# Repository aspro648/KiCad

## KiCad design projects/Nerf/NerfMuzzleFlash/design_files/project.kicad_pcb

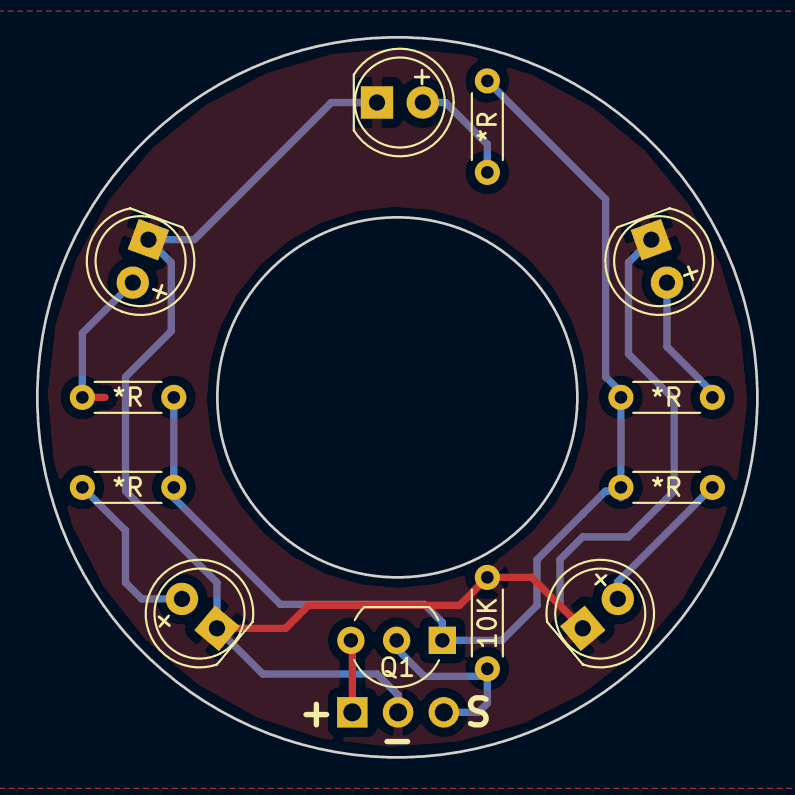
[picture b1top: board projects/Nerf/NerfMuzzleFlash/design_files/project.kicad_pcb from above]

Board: 2 copper layers, 40.0 x 40.0 mm, 13 parts (0 on the bottom side), 9 nets.

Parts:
D1, D2, D3, D4, D5: LED; LED_D5.0mm
J1: CONN_01X03; Pin_Header_Straight_1x03_Pitch2.54mm
Q1: TN0702; TO-92_Inline_Wide
R1, R2, R3, R4, R5: *R; R_Axial_P5.08mm
R6: 10K; R_Axial_P5.08mm

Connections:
GND: D1.1, D2.1, D3.1, D4.1, D5.1, J1.2, R6.1
unnamed: D1.2, R1.1
unnamed: D2.2, R2.1
unnamed: D3.2, R3.1
unnamed: D4.2, R4.1
unnamed: D5.2, R5.1
unnamed: J1.1, Q1.3
unnamed: J1.3, Q1.2, R6.2
unnamed: Q1.1, R1.2, R2.2, R3.2, R4.2, R5.2

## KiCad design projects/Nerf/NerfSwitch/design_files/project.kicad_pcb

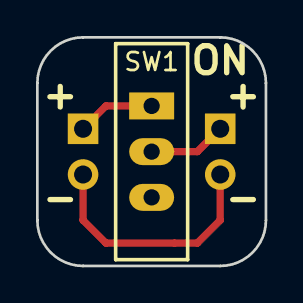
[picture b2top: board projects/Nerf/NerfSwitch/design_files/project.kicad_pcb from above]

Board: 2 copper layers, 12.7 x 12.7 mm, 3 parts (0 on the bottom side), 3 nets.

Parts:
J1, J2: CONN_01X02; Pin_Header_Straight_1x02_Pitch2.54mm
SW1: SW_SPST; SW_CuK_OS102011MA1QN1_SPDT_Angled

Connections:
unnamed: J1.1, SW1.1
unnamed: J1.2, J2.2
unnamed: J2.1, SW1.2

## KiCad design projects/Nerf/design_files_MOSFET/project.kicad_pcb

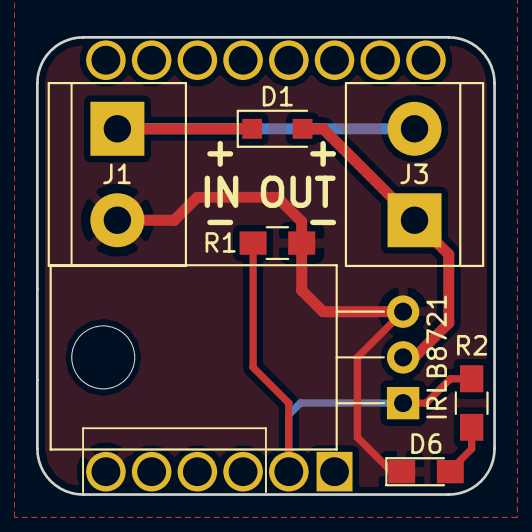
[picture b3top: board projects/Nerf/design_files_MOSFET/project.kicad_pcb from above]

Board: 2 copper layers, 25.4 x 25.4 mm, 10 parts (0 on the bottom side), 5 nets.

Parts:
D1: D; D_SOD-123F
D6: LED; LED_0805_HandSoldering
J1, J3: Conn_01x02; TerminalBlock_bornier-2_P5.08mm
J2: Beetje_Bottom
J4: Beetje_Top
Q1: IRLB8721; TO-220-3_Horizontal
R1: 10K; R_0805_HandSoldering
R2: 1K; R_0805_HandSoldering
VAL: MadeInOregonRev25

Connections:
/D6: J2.2, Q1.1, R1.1, R2.2
GND: D6.1, J1.2, J2.6, Q1.3, R1.2
unnamed: D1.1, J1.1, J3.2
unnamed: D1.2, J3.1, Q1.2
unnamed: D6.2, R2.1

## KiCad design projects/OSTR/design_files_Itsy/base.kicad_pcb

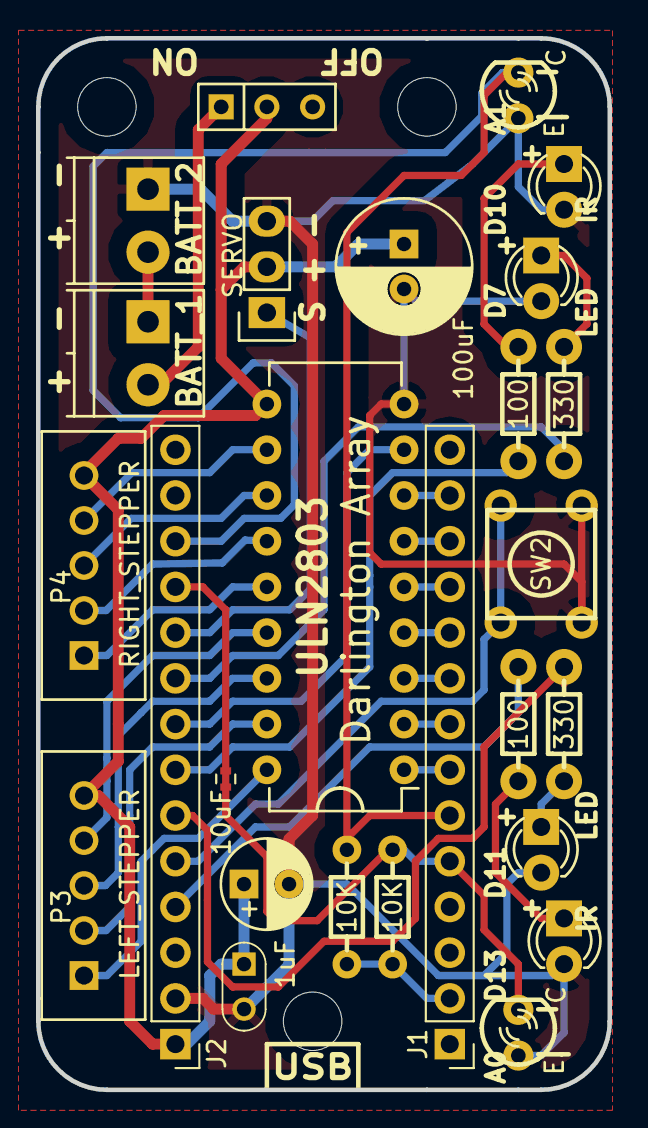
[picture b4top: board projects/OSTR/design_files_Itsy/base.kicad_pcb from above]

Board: 2 copper layers, 31.8 x 58.4 mm, 32 parts (1 on the bottom side), 33 nets.

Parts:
C1: 100uF; C_Radial_D7.5_L11.2_P2.5
C2: 10uF; C_Radial_D5_L11_P2.5
C3: 1uF; C_Disc_D3_P2.5
D2: IR_LED; LED-3MM
D3, D4: LED; LED-3MM
D5: IR LED; LED-3MM
J1: Isty_Left; Pin_Header_Straight_1x14_Pitch2.54mm
J2: Itsy_right; Pin_Header_Straight_1x14_Pitch2.54mm
P3: LEFT_STEPPER; JST_B5B-XH-A
P4: RIGHT_STEPPER; JST_B5B-XH-A
P5: BATT1; TerminalBlock_Pheonix_PT-3.5mm_2pol
P6: BATT2; TerminalBlock_Pheonix_PT-3.5mm_2pol
P7: SERVO; Pin_Header_Straight_1x03
P9, P9#2, P9#3: CONN_01X01; Lego_Pad
Q1, Q2: OPTO_NPN; PHOTOTRANS
R1, R8: 0; R_0402
R2, R5: 100; Resistor_Horz
R3, R4: 330; Resistor_Horz
R6, R7: 10K; Resistor_Horz
SW1: SPST; SW_Micro_SPST
SW2: SW_PUSH; SW_PUSH_SMALL
U1: ULN2803; DIP-18_W7.62mm
VAL: MadeInOregonRev25
VAL#2: MB225rev

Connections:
+3V3: J1.2, R6.1, R7.1
/A0: J1.5, J2.11, Q2.3, R6.2, R8.1, R8.2
/A1: J1.6, J2.12, Q1.3, R1.1, R1.2, R7.2
/A2: J1.7, U1.1
/A3: J1.8, U1.2
/A4: J1.9, U1.3
/A5: J1.10, U1.4
/BAT: C1.1, C2.1, C3.1, J2.1, P3.5, P4.5, P7.2, SW1.2, U1.10
/D5: J2.10, P7.1
/D7: J2.9, R3.1
/D9: J2.8, U1.8
/D10: J2.7, R5.1
/D11: J2.6, R4.1
/D12: J2.5, SW2.1
/D13: J2.4, R2.1
/D14: J1.13, U1.7
/D15: J1.11, U1.5
/D16: J1.12, U1.6
GND: C1.2, C2.2, C3.2, D2.1, D3.1, D4.1, D5.1, J2.2, P5.1, P7.3, Q1.1, Q2.1, SW2.2, U1.9
unnamed: D2.2, R2.2
unnamed: D3.2, R3.2
unnamed: D4.2, R4.2
unnamed: D5.2, R5.2
unnamed: P3.1, U1.18
unnamed: P3.2, U1.17
unnamed: P3.3, U1.16
unnamed: P3.4, U1.15
unnamed: P4.1, U1.14
unnamed: P4.2, U1.13
unnamed: P4.3, U1.12
unnamed: P4.4, U1.11
unnamed: P5.2, P6.1
unnamed: P6.2, SW1.1

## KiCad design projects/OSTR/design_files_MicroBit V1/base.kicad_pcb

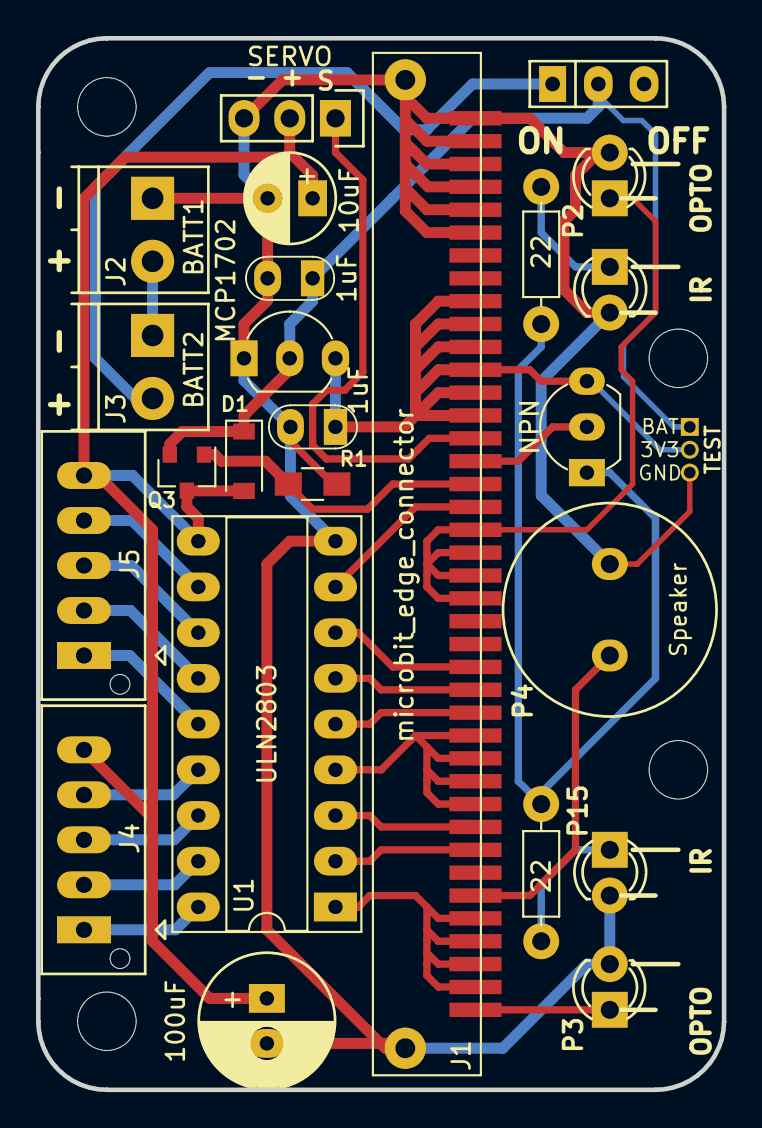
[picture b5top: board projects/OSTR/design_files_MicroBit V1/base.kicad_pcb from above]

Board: 2 copper layers, 38.1 x 58.4 mm, 31 parts (0 on the bottom side), 31 nets.

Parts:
C1: 100uF; C_Radial_D7.5_L11.2_P2.5
C2: 10uF; C_Radial_D5_L11_P2.5
C3, C4: 1uF; C_Disc_D3_P2.5
D1: D; D_SOD-123
D2: IR_LED; LED-3MM
D5: IR LED; LED-3MM
J1: microbit_edge_connector; MicroBit40
J2: BATT1; TerminalBlock_Pheonix_PT-3.5mm_2pol
J3: BATT2; TerminalBlock_Pheonix_PT-3.5mm_2pol
J4: LEFT_STEPPER; JST_B5B-XH-A
J5: RIGHT_STEPPER; JST_B5B-XH-A
J6: SERVO; Pin_Header_Straight_1x03
J7: TEST; Pin_Header_Straight_1x03_Pitch1.27mm
LS1: Speaker; SPEAKER
P9, P9#2, P9#3, P9#4: CONN_01X01; Lego_Pad
Q1, Q2: OPTO; LED-3MM
Q3: MOSFET; SOT-23
Q4: NPN; TO-92_Inline_Wide
R1: 10K; R_0805_HandSoldering
R2, R5: 22; R__7.62mm
SW1: SPST; SW_Micro_SPST
U1: ULN2803; DIP-18_W7.62mm_Socket_LongPads
U2: MCP1702; TO-92_Inline_Wide
VAL: MadeInOregonRev25
VAL#2: MB225rev

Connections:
+3V3: C3.1, J1.17, J1.19, J1.21, J1.23, J1.25, J1.27, J7.2, Q4.3, U2.3
/BAT: C4.1, D1.1, J7.1, Q3.2, SW1.2, U2.2
/P0: J1.71, J1.73, J1.75, J1.77, U1.1
/P1: J1.55, J1.57, J1.59, J1.61, U1.4
/P2: J1.37, J1.39, J1.41, J1.43, Q1.3
/P3: J1.79, Q2.3
/P4: J1.69, LS1.1
/P6: J1.65, U1.2
/P7: J1.63, U1.3
/P8: J1.53, U1.5
/P9: J1.51, U1.6
/P10: J1.49, U1.7
/P13: J1.35, U1.8
/P14: J1.33, Q3.1, R1.1
/P15: J1.31, Q4.2
/P16: J1.29, J6.1
GND: C1.2, C2.2, C3.2, C4.2, D2.1, D5.1, J1.1, J1.3, J1.5, J1.7, J1.9, J1.11, J2.1, J6.3, J7.3, LS1.2, Q1.1, Q2.1, R1.2, U1.9, U2.1
unnamed: C1.1, C2.1, D1.2, J4.5, J5.5, J6.2, Q3.3, U1.10
unnamed: D2.2, R2.2
unnamed: D5.2, R5.2
unnamed: J2.2, J3.1
unnamed: J3.2, SW1.1
unnamed: J4.1, U1.18
unnamed: J4.2, U1.17
unnamed: J4.3, U1.16
unnamed: J4.4, U1.15
unnamed: J5.1, U1.14
unnamed: J5.2, U1.13
unnamed: J5.3, U1.12
unnamed: J5.4, U1.11
unnamed: Q4.1, R2.1, R5.1

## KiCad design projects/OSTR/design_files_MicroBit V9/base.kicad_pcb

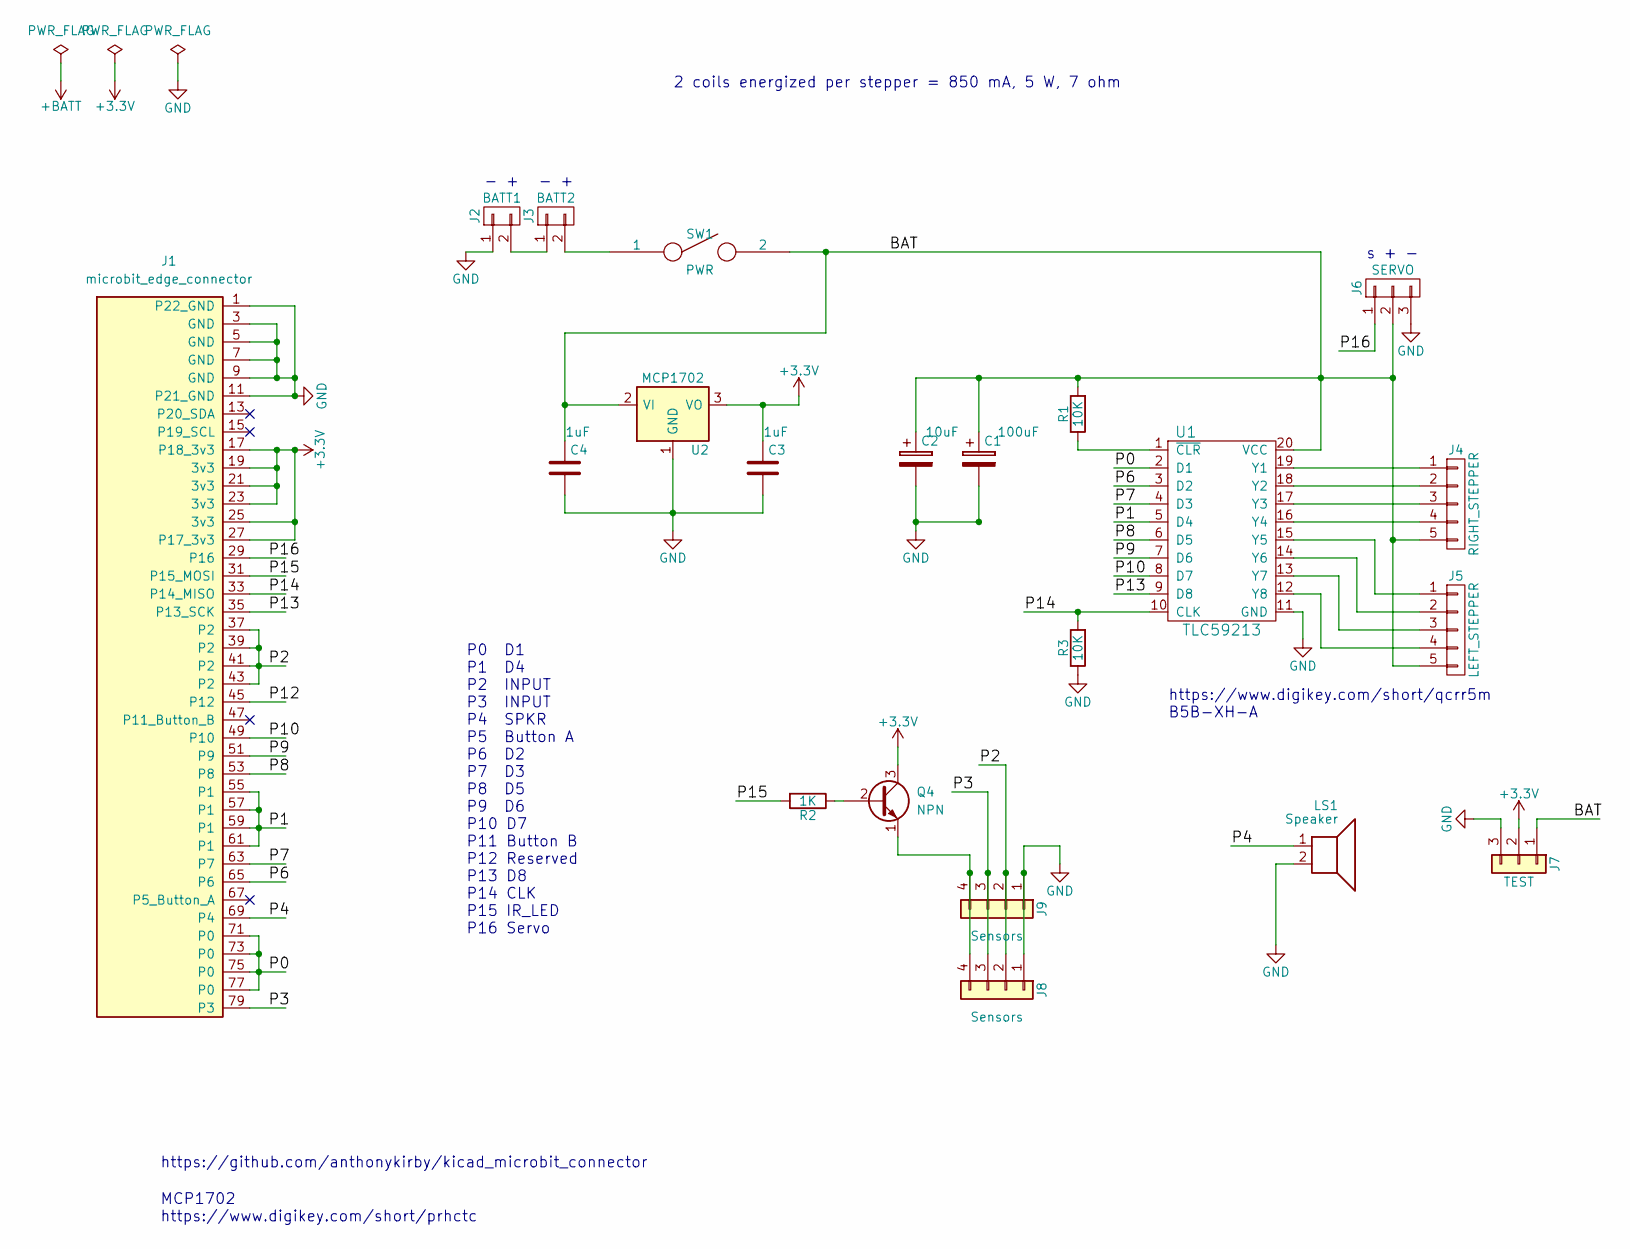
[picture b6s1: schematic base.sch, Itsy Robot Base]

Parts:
C1: 100uF; C_Radial_D7.5_L11.2_P2.5
C2: 10uF; C_Radial_D5_L11_P2.5
C3, C4: 1uF; C_Disc_D3_P2.5
J1: microbit_edge_connector; MicroBit40
J2: BATT1; TerminalBlock_Pheonix_PT-3.5mm_2pol
J3: BATT2; TerminalBlock_Pheonix_PT-3.5mm_2pol
J4: RIGHT_STEPPER; JST_B5B-XH-A
J5: LEFT_STEPPER; JST_B5B-XH-A
J6: SERVO; Pin_Header_Straight_1x03
J7: TEST; Pin_Header_Straight_1x03_Pitch1.27mm
J8: Sensors; Pin_Header_Straight_1x04_Pitch2.54mm
J9: Sensors; Pin_Header_Angled_1x04_Pitch2.54mm
LS1: Speaker; SPEAKER
Q4: NPN; TO-92_Inline_Wide
R1, R3: 10K; R__7.62mm
R2: 1K; R__7.62mm
SW1: PWR; SW_Micro_SPST
U1: TLC59213; DIP-20_W7.62mm_LongPads
U2: MCP1702; TO-92_Inline_Wide

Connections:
+3V3: C3.1, J1.17 (P18_3v3), J1.19 (3v3), J1.21 (3v3), J1.23 (3v3), J1.25 (3v3), J1.27 (P17_3v3), J7.2, Q4.3 (C), U2.3 (VO)
/BAT: C1.1, C2.1, C4.1, J4.5, J5.5, J6.2, J7.1, R1.2, SW1.2, U1.20 (VCC), U2.2 (VI)
/P0: J1.71 (P0), J1.73 (P0), J1.75 (P0), J1.77 (P0), U1.2 (D1)
/P1: J1.55 (P1), J1.57 (P1), J1.59 (P1), J1.61 (P1), U1.5 (D4)
/P2: J1.37 (P2), J1.39 (P2), J1.41 (P2), J1.43 (P2), J8.2, J9.2
/P3: J1.79 (P3), J8.3, J9.3
/P4: J1.69 (P4), LS1.1
/P6: J1.65 (P6), U1.3 (D2)
/P7: J1.63 (P7), U1.4 (D3)
/P8: J1.53 (P8), U1.6 (D5)
/P9: J1.51 (P9), U1.7 (D6)
/P10: J1.49 (P10), U1.8 (D7)
/P12: J1.45 (P12)
/P13: J1.35 (P13_SCK), U1.9 (D8)
/P14: J1.33 (P14_MISO), R3.2, U1.10 (CLK)
/P15: J1.31 (P15_MOSI), R2.2
/P16: J1.29 (P16), J6.1
GND: C1.2, C2.2, C3.2, C4.2, J1.1 (P22_GND), J1.3 (GND), J1.5 (GND), J1.7 (GND), J1.9 (GND), J1.11 (P21_GND), J2.1, J6.3, J7.3, J8.1, J9.1, LS1.2, R3.1, U1.11 (GND), U2.1 (GND)
unnamed: J2.2, J3.1
unnamed: J3.2, SW1.1
unnamed: J4.1, U1.19 (Y1)
unnamed: J4.2, U1.18 (Y2)
unnamed: J4.3, U1.17 (Y3)
unnamed: J4.4, U1.16 (Y4)
unnamed: J5.1, U1.15 (Y5)
unnamed: J5.2, U1.14 (Y6)
unnamed: J5.3, U1.13 (Y7)
unnamed: J5.4, U1.12 (Y8)
unnamed: J8.4, J9.4, Q4.1 (E)
unnamed: Q4.2 (B), R2.1
unnamed: R1.1, U1.1 (~CLR)

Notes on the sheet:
https://www.digikey.com/short/qcrr5m B5B-XH-A
- +
s + -
https://github.com/anthonykirby/kicad_microbit_connector
MCP1702 https://www.digikey.com/short/prhctc
2 coils energized per stepper = 850 mA, 5 W, 7 ohm
P0 D1 P1 D4 P2 INPUT P3 INPUT P4 SPKR P5 Button A P6 D2 P7 D3 P8 D5 P9 D6 P10 D7 P11 Button B P12 Reserved P13 D8 P14 CLK P15 IR_LED P16 Servo

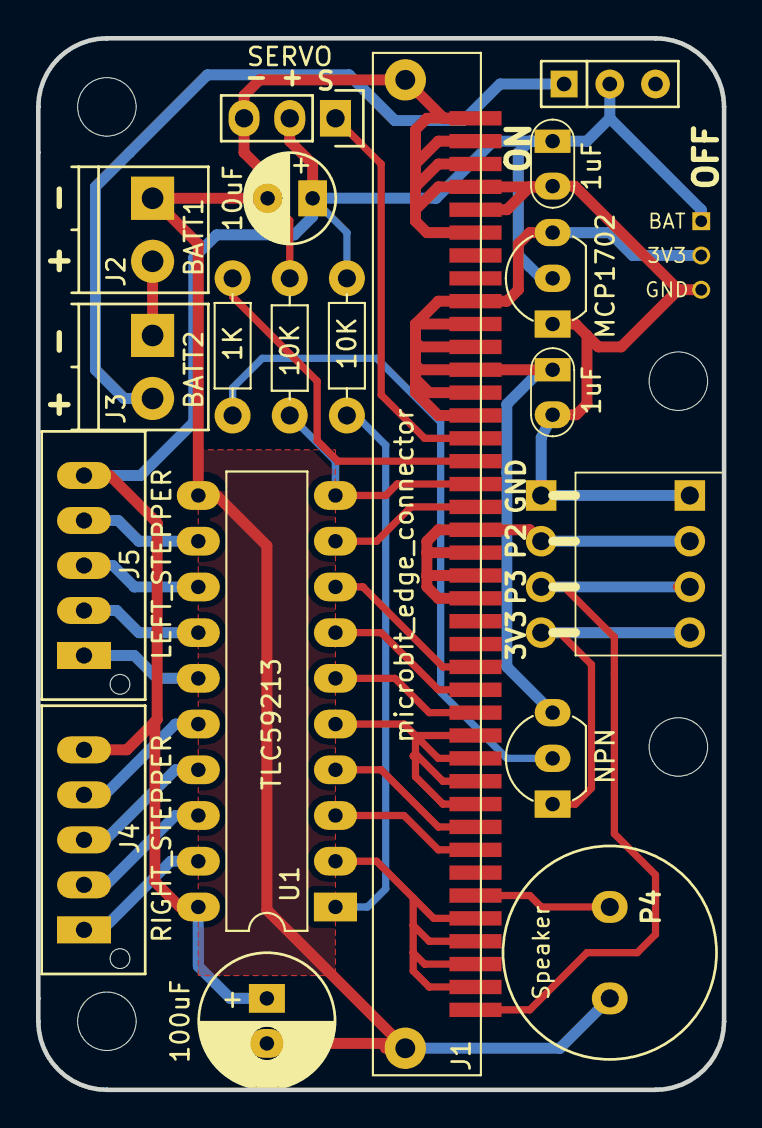
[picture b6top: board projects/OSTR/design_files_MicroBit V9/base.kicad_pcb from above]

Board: 2 copper layers, 38.1 x 58.4 mm, 27 parts (1 on the bottom side), 30 nets.

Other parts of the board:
P9, P9#2, P9#3, P9#4: CONN_01X01; Lego_Pad
VAL: MadeInOregonRev25
VAL#2: MB225rev
